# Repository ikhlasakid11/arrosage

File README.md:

# Arrosage

Projet electronique KiCad 10. Ouvrir `arrosage.kicad_pro`.

Le schema principal `arrosage.kicad_sch` utilise trois sous-feuilles :
`untitled.kicad_sch` (radio), `BQ25570.kicad_sch` (alimentation) et
`capteur.kicad_sch`. `mic.kicad_sch` est conserve comme feuille de travail.

Les symboles et empreintes personnalises sont inclus dans `symbols/` et
`footprints/`. Les tables de bibliotheques utilisent `${KIPRJMOD}` : aucune
dependance au dossier externe `pot_fleur` n'est necessaire pour ces empreintes.
Les bibliotheques standard de KiCad doivent etre installees.

Les empreintes de l'antenne `SmartPot_RF:CST_IFA_868MHz_SmartPot` et de la
bobine `LPS4018-223MRC:IND_LPS4018-223MRC` ont ete recuperees dans la copie
locale de `SmartPot_RAK3172/old/pot_fleur`, sans modification de leur geometrie.
Le modele 3D optionnel `3dmodels/LPS4018-223MRC.step` n'etait pas fourni ;
son absence n'empeche pas l'utilisation de l'empreinte PCB.

La bibliotheque SHT40 provient du pack local SHT40_KiCad. Ses instructions
et attributions sont conservees dans `docs/SHT40_LIRE_MOI.txt`
(bibliotheques KiCad, CC-BY-SA 4.0 avec exception KiCad).
Les autres fichiers conservent leurs attributions et conditions d'origine ;
aucune nouvelle licence generale n'est attribuee.

Les sauvegardes `.history/` et preferences personnelles sont ignorees par Git.
Le projet est en cours : cette preparation pour GitHub ne valide pas la
conception electrique ni l'aptitude du PCB a la fabrication.

L'antenne CST du projet est importee sous la reference **A2**, dans la
bibliotheque `Arrosage_RF`. Voir [les cotes, raccords et limites de l'import](docs/A2_IFA_868MHz_CST.md).

La carte est maintenant placee et routee en **35 x 55 mm, deux couches,
epaisseur 1,6 mm**, avec 25 % de la surface reservee a l'antenne.
La **version test du 25 novembre 2026** place l'U.FL sur le trajet RF, ajoute
les reperes en serigraphie, degage le bornier solaire et retire les sept
resistances alternatives inutiles. Voir [les modifications et controles de
la version test](docs/TEST_35x55.md), les vues du PCB et le plan d'implantation.
Le DRC et la parite schema/PCB sont sans violation ni connexion manquante.
La validation radio et les points electriques signales sur J19 et EN restent
necessaires avant fabrication finale.

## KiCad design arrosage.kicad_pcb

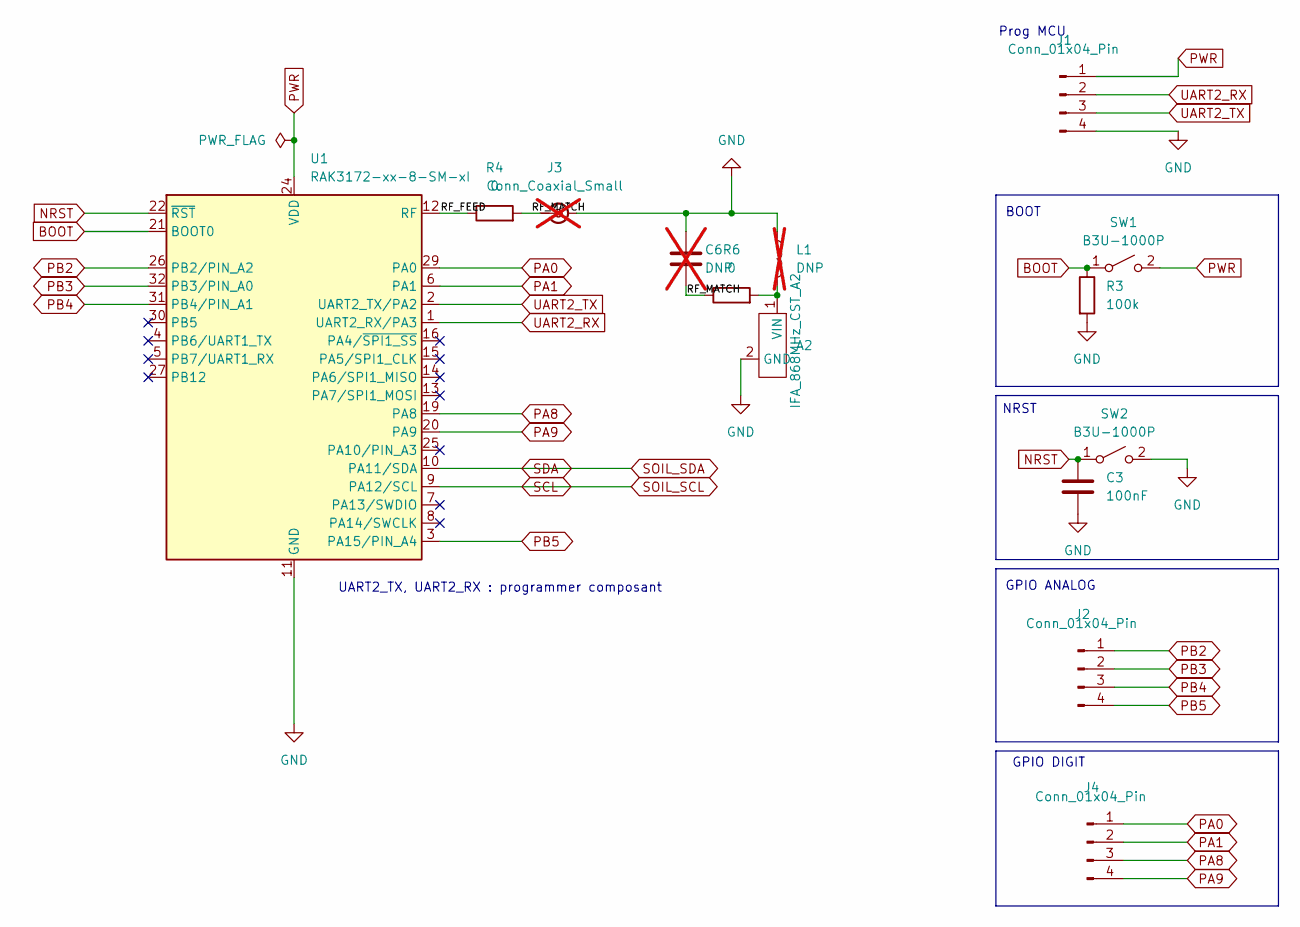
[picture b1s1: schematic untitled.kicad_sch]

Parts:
A2: IFA_868MHz_CST_A2; A2_IFA_868MHz_CST
C3: 100nF; C_0603_1608Metric
C6: DNP; C_0603_1608Metric; not fitted
J1, J2, J4: Conn_01x04_Pin; PinHeader_1x04_P2.54mm_Vertical
J3: Conn_Coaxial_Small; U.FL_Hirose_U.FL-R-SMT-1_Vertical; not fitted
L1: DNP; L_0603_1608Metric; not fitted
R3: 100k; R_0603_1608Metric
R4, R6: 0; R_0603_1608Metric
SW1, SW2: B3U-1000P; SW_SPST_B3U-1000P
U1: RAK3172-xx-8-SM-xI; RAK3172

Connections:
/Microcontroleur/RF_FEED: R4.1, U1.12 (RF)
/Microcontroleur/RF_MATCH: C6.2, J3.1 (In), R4.2, R6.1
BOOT: R3.1, SW1.1 (A), U1.21 (BOOT0)
GND: A2.2 (GND), C3.2, C6.1, J1.4, J3.2 (Ext), L1.1, R3.2, SW2.2 (B), U1.11 (GND), U1.17 (GND), U1.18 (GND), U1.23 (GND), U1.28 (GND); also elsewhere on the board
NRST: C3.1, SW2.1 (A), U1.22 (~RST)
unnamed: A2.1 (VIN), L1.2, R6.2
PA0: J4.1, U1.29 (PA0)
PA1: J4.2, U1.6 (PA1)
PA8: J4.3, U1.19 (PA8)
PA9: J4.4, U1.20 (PA9)
PB2: J2.1, U1.26 (PB2/PIN_A2)
PB3: J2.2, U1.32 (PB3/PIN_A0)
PB4: J2.3, U1.31 (PB4/PIN_A1)
PB5: J2.4, U1.3 (PA15/PIN_A4)
PWR: J1.1, SW1.2 (B), U1.24 (VDD); also elsewhere on the board
SCL: U1.9 (PA12/SCL); also elsewhere on the board
SDA: U1.10 (PA11/SDA); also elsewhere on the board
UART2_RX: J1.2, U1.1 (UART2_RX/PA3)
UART2_TX: J1.3, U1.2 (UART2_TX/PA2)

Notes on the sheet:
Prog MCU
BOOT
UART2_TX, UART2_RX : programmer composant
GPIO ANALOG
GPIO DIGIT
NRST

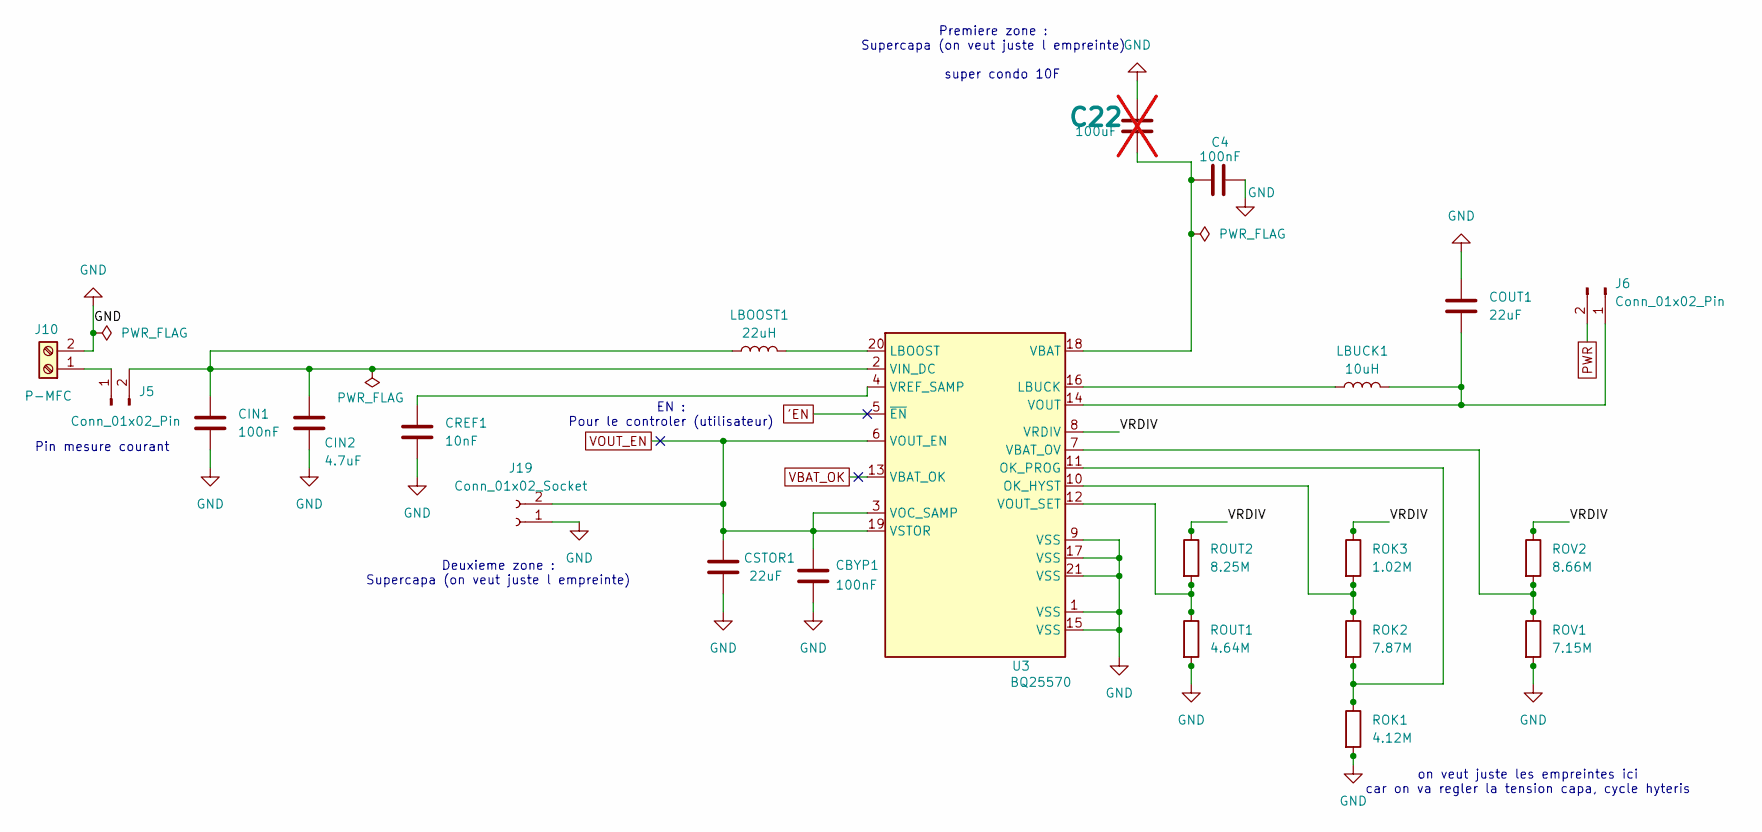
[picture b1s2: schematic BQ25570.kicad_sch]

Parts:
C4: 100nF; C_0603_1608Metric; LCSC C1591
C22: 100uF; C_0603_1608Metric; not fitted
CBYP1: 100nF; C_0603_1608Metric; LCSC C1591
CIN1: 100nF; C_0603_1608Metric; LCSC C1591
CIN2: 4.7uF; C_0603_1608Metric; LCSC C107368
COUT1: 22uF; C_0603_1608Metric; LCSC C2762594
CREF1: 10nF; C_0603_1608Metric; LCSC C1591
CSTOR1: 22uF; C_0603_1608Metric; LCSC C2762594
J5, J6: Conn_01x02_Pin; PinHeader_1x02_P2.54mm_Vertical; LCSC C3332353
J10: P-MFC; TerminalBlock_Phoenix_MKDS-3-2-5.08_1x02_P5.08mm_Horizontal; LCSC C2683165
J19: Conn_01x02_Socket; PinSocket_1x02_P2.54mm_Vertical; LCSC C5372032
LBOOST1: 22uH; IND_LPS4018-223MRC; LCSC C5441602
LBUCK1: 10uH; L_1008_2520Metric; LCSC C237599
ROK1: 4.12M; R_0603_1608Metric; LCSC C3009313
ROK2: 7.87M; R_0603_1608Metric; LCSC C482913
ROK3: 1.02M; R_0603_1608Metric; LCSC C2930138
ROUT1: 4.64M; R_0603_1608Metric; LCSC C2079741
ROUT2: 8.25M; R_0603_1608Metric; LCSC C166757
ROV1: 7.15M; R_0603_1608Metric; LCSC C422907
ROV2: 8.66M; R_0603_1608Metric; LCSC C4087386
U3: BQ25570; QFN-20-1EP_3.5x3.5mm_P0.5mm_EP2x2mm; LCSC C506250

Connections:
'EN: U3.5 (~EN)
/BQ25570/VRDIV: ROK3.1, ROUT2.1, ROV2.1, U3.8 (VRDIV)
GND: C4.2, C22.2, CBYP1.2, CIN1.2, CIN2.2, COUT1.1, CREF1.2, CSTOR1.2, J10.2, J19.1, ROK1.2, ROUT1.2, ROV1.2, U3.1 (VSS), U3.9 (VSS), U3.15 (VSS), U3.17 (VSS), U3.21 (VSS); also elsewhere on the board
unnamed: CIN1.1, CIN2.1, J5.2, LBOOST1.1, U3.2 (VIN_DC)
unnamed: COUT1.2, J6.1, LBUCK1.2, U3.14 (VOUT)
unnamed: J5.1, J10.1
unnamed: LBOOST1.2, U3.20 (LBOOST)
unnamed: LBUCK1.1, U3.16 (LBUCK)
unnamed: ROK2.1, ROK3.2, U3.10 (OK_HYST)
unnamed: ROK1.1, ROK2.2, U3.11 (OK_PROG)
unnamed: C4.1, C22.1, U3.18 (VBAT)
unnamed: ROV1.1, ROV2.2, U3.7 (VBAT_OV)
unnamed: ROUT1.1, ROUT2.2, U3.12 (VOUT_SET)
unnamed: CREF1.1, U3.4 (VREF_SAMP)
PWR: J6.2; also elsewhere on the board
VBAT_OK: U3.13 (VBAT_OK)
VOUT_EN: CBYP1.1, CSTOR1.1, J19.2, U3.3 (VOC_SAMP), U3.6 (VOUT_EN), U3.19 (VSTOR)

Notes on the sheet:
EN : Pour le controler (utilisateur)
super condo 10F
Deuxieme zone : Supercapa (on veut juste l empreinte)
on veut juste les empreintes ici car on va regler la tension capa, cycle hyteris
Premiere zone : Supercapa (on veut juste l empreinte)
Pin mesure courant

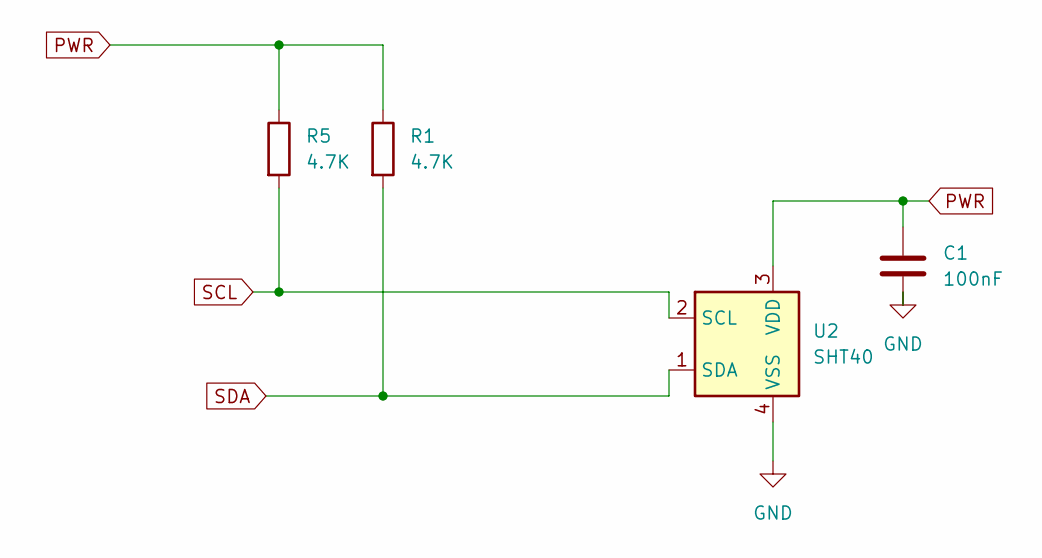
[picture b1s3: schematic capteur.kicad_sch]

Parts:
C1: 100nF; C_0603_1608Metric
R1, R5: 4.7K; R_0603_1608Metric
U2: SHT40; SHT40_DFN4

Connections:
GND: C1.2, U2.4 (VSS); also elsewhere on the board
PWR: C1.1, R1.1, R5.1, U2.3 (VDD); also elsewhere on the board
SCL: R5.2, U2.2 (SCL); also elsewhere on the board
SDA: R1.2, U2.1 (SDA); also elsewhere on the board

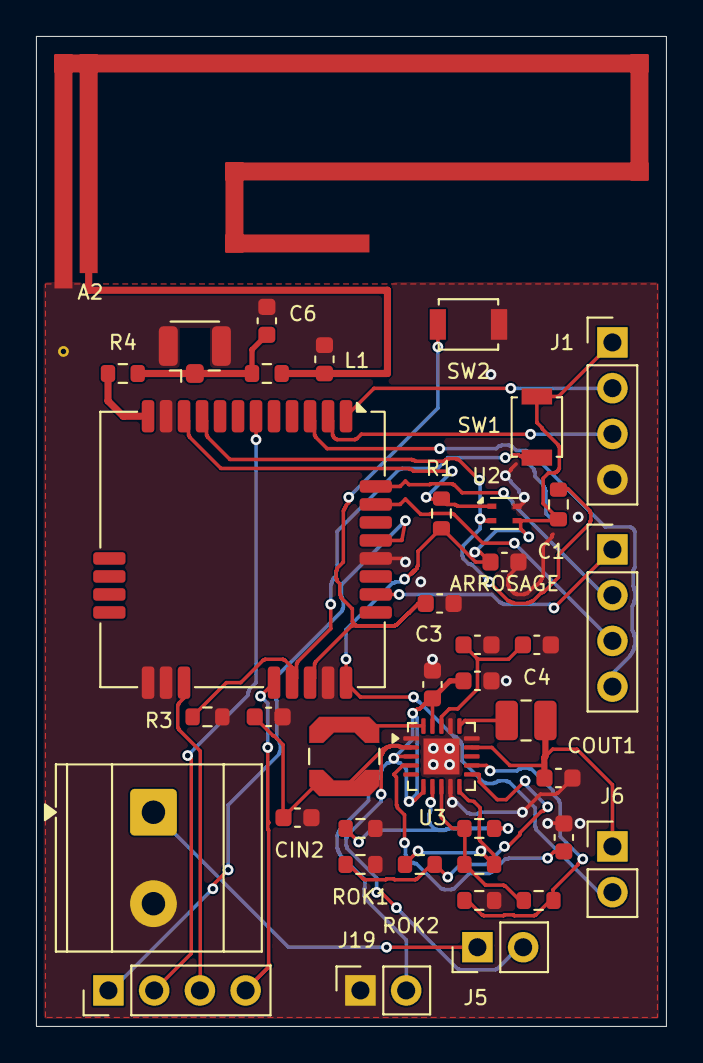
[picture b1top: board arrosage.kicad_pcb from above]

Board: 2 copper layers, 35.0 x 55.0 mm, 40 parts (0 on the bottom side), 32 nets.
